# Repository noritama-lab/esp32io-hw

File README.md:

# ESP32-S3 IO Device – Hardware Repository

このリポジトリは、ESP32-S3 を産業用途で扱うための  
**入出力回路（KiCad）** と **筐体データ（FreeCAD / 3MF / STEP）** を公開するものです。

本プロジェクトは、電子工作レベルではなく、  
**工場の 24V 機器と安全に接続できる小型 I/O デバイス**  
として利用できることを目標に設計しています。

> ⚠️ 本リポジトリは個人開発によるものであり、認証・第三者検証を受けたものではありません。  
> 実運用前には、必ずご自身の環境・負荷条件に対する検証を行ってください。詳しくは [免責事項](#️-免責事項--disclaimer) を参照してください。

このハードウェアは、以下のソフトウェア群と組み合わせて使用することを想定しています。  
This hardware is designed to work together with the following software components.

- 🔧 HTTP版ファームウェア: [esp32io-firmware](https://github.com/noritama-lab/esp32io-firmware) — WiFi/HTTP経由での制御版
- 🐍 HTTP版 Pythonクライアント: [esp32io](https://pypi.org/project/esp32io/) — PyPI公開
- 🔧 MQTT版ファームウェア: [esp32io-mqtt-firmware](https://github.com/noritama-lab/esp32io-mqtt-firmware) — MQTT + Home Assistant対応ファームウェア
- 🐍 MQTT版 Pythonクライアント: [esp32io-mqtt](https://pypi.org/project/esp32io-mqtt/) — PyPI公開

---

# ESP32-S3 IO Device – Hardware Repository (English)

This repository provides the **hardware design (KiCad)** and **mechanical data (FreeCAD / 3MF / STEP)**  
for an ESP32-S3 based I/O device intended for **industrial 24V environments**.

The goal of this project is to create a compact I/O module that can be safely connected  
to factory equipment, rather than a hobby-level electronics board.

> ⚠️ This is an individually developed, open-source project. It has not been certified or independently verified.  
> Please validate the design against your own environment and load conditions before deploying it in production. See [Disclaimer](#️-disclaimer) below.

This hardware is designed to be used together with:

- 🔧 HTTP firmware: [esp32io-firmware](https://github.com/noritama-lab/esp32io-firmware) — WiFi/HTTP control variant
- 🐍 HTTP Python client: [esp32io](https://pypi.org/project/esp32io/) — Published on PyPI
- 🔧 MQTT firmware: [esp32io-mqtt-firmware](https://github.com/noritama-lab/esp32io-mqtt-firmware) — MQTT-based firmware with Home Assistant support
- 🐍 MQTT Python client: [esp32io-mqtt](https://pypi.org/project/esp32io-mqtt/) — Published on PyPI

---

## 含まれるデータ / Included Data

### ■ KiCad（回路図・基板） / KiCad (Schematics & PCB)
- `ESP32-S3-IO-DEVICE.kicad_sch` – 回路図 / Schematic  
- `ESP32-S3-IO-DEVICE.kicad_pcb` – 基板データ / PCB layout  
- `ESP32-S3-IO-DEVICE.kicad_pro` – プロジェクト設定 / Project settings  
- `sym-lib-table` / `fp-lib-table` – ライブラリ設定 / Library tables  

KiCad プロジェクトを開くだけで、  
**回路図 → 基板 → ガーバー** まで完全に再現できます。  
Opening the KiCad project allows full reproduction from **schematic → PCB → Gerber**.

基板自体はHTTP版・MQTT版どちらのファームウェアでも共通してお使いいただけます。  
The same PCB can be used with either the HTTP or MQTT firmware.

---

### ■ FreeCAD / 3D データ（筐体・取付板）  
### FreeCAD / 3D Data (Enclosure & Mounting Parts)
- `.FCStd` – FreeCAD モデル / FreeCAD models  
- `.3mf` – 3D プリント用 / For 3D printing  
- `.step` – 汎用 CAD 形式 / Standard CAD format  

ケース、基板カバー、取付板など、  
**デバイスとして使える形にするための筐体データ**を含みます。  
Includes mechanical parts required to assemble the device.

> ℹ️ 基板取付板は現行基板でもそのままご利用いただけます。  
> 基板カバーのみ旧基板に合わせた設計のため、現行基板とは適合しない場合があります。  
> 最新基板に対応した基板カバーは今後更新予定です。
>
> ℹ️ The board mounting plate is compatible with the current PCB as-is.  
> Only the board cover was designed for an older board revision and may not fit the current PCB.  
> An updated cover matching the latest board will be published in the future.

---

## 🏭 工場で使うための設計方針  
## Industrial Design Principles

本デバイスは、一般的な電子工作向けではなく、  
**工場・設備で使われる 24V 系信号を安全に扱うための回路構成**を採用しています。  
This device is designed for **industrial 24V signals**, not hobby electronics.

### ✔ DIO_OUT：NPN シンク出力 / NPN Sink Output  
PLC と同じ方式で外部ソース負荷を駆動可能。  
Compatible with PLC-style sourcing loads.

### ✔ DIO_IN：ソース入力（NPN シンク出力センサ対応）  
### Source Input (for NPN sensors)  
**トランジスタ＋抵抗＋Zener** による保護回路を採用。  
Protected using **transistor + resistors + Zener**.

### ✔ ADC：0〜10V アナログ入力 / 0–10V Analog Input  
工場のアナログ信号に合わせて **分圧＋可変抵抗＋Zener** を使用。  
Uses **voltage divider + trim resistor + Zener** for safe conversion.

> ℹ️ DI/DOはフォトカプラによりMCU側と絶縁されていますが、ADC（アナログ入力）は非絶縁です。  
> ℹ️ DI/DO channels are isolated from the MCU via optocouplers. The ADC (analog input) is **not** isolated.

### ✔ PWM：3.3V ロジック出力 / 3.3V Logic PWM  
外部ドライバ・SSR の制御信号として使用。  
Used as a control signal for external drivers or SSRs.

---

## ⚙️ 想定負荷 / Intended Load

DIO_OUT（NPNシンク出力）は、以下のような **小型DC24Vリレー** の直接駆動を想定して設計・検証しています。  
The DIO_OUT (NPN sink output) is designed and verified for driving **small DC24V relays**, such as:

- オムロン LYシリーズ相当（コイル電流 目安 20〜40mA程度） / Omron LY-series relays or equivalent (coil current approx. 20–40mA)

より大きな消費電流のソレノイド・コンタクタ・AC駆動機器を直接駆動することは想定していません。  
それらを制御する場合は、SSRやパワーリレーなど適切な中間段を介してください。  
Larger solenoids, contactors, or AC-driven devices are **not** intended to be driven directly.  
Use an appropriate intermediate stage (e.g. SSR or power relay) for such loads.

複数チャンネルを同時にON にする場合、COM+ライン全体に流れる電流（チャンネル数 × コイル電流）が、  
使用する電源・配線の許容電流を超えないことをご確認ください。  
When switching multiple channels simultaneously, verify that the total current on the COM+ line  
(number of channels × coil current) does not exceed the current rating of your power supply and wiring.

---

## ディレクトリ構成 / Directory Structure
/KiCad
/3D_print

> 📷 組み立て後の完成写真、および使用部品表（BOM）は準備中です。追って追加予定です。  
> 📷 Assembly photos and a bill of materials (BOM) are planned and will be added soon.

---

## 必要なソフトウェア / Required Software

- KiCad 7+  
- FreeCAD 0.21+  
- 3D プリンタ（任意） / Any 3D printer (FDM recommended)

---

## ⚠️ 免責事項 / Disclaimer

本リポジトリで公開する回路・筐体データは、個人による設計・検証であり、  
特定の安全規格・産業規格への適合を保証するものではありません。  
実際の設備・機器へ接続する場合は、電圧・電流・絶縁・保護協調などについて、  
利用者ご自身の責任において十分な検証を行ってください。  
本データの利用によって生じたいかなる損害についても、作者は責任を負いません。

The circuit and enclosure data provided in this repository are individually designed and verified,  
and do not guarantee compliance with any specific safety or industrial standard.  
Before connecting this device to actual equipment, users are solely responsible for verifying  
voltage, current, isolation, and protection coordination appropriate to their environment.  
The author assumes no liability for any damage resulting from the use of this data.

---

## ライセンス / License

- 回路図・基板データ（KiCad）: MIT License  
- 3D モデル（FreeCAD / STEP / 3MF）: CC BY-SA 4.0  

- Schematic & PCB (KiCad): MIT License  
- 3D Models (FreeCAD / STEP / 3MF): CC BY-SA 4.0

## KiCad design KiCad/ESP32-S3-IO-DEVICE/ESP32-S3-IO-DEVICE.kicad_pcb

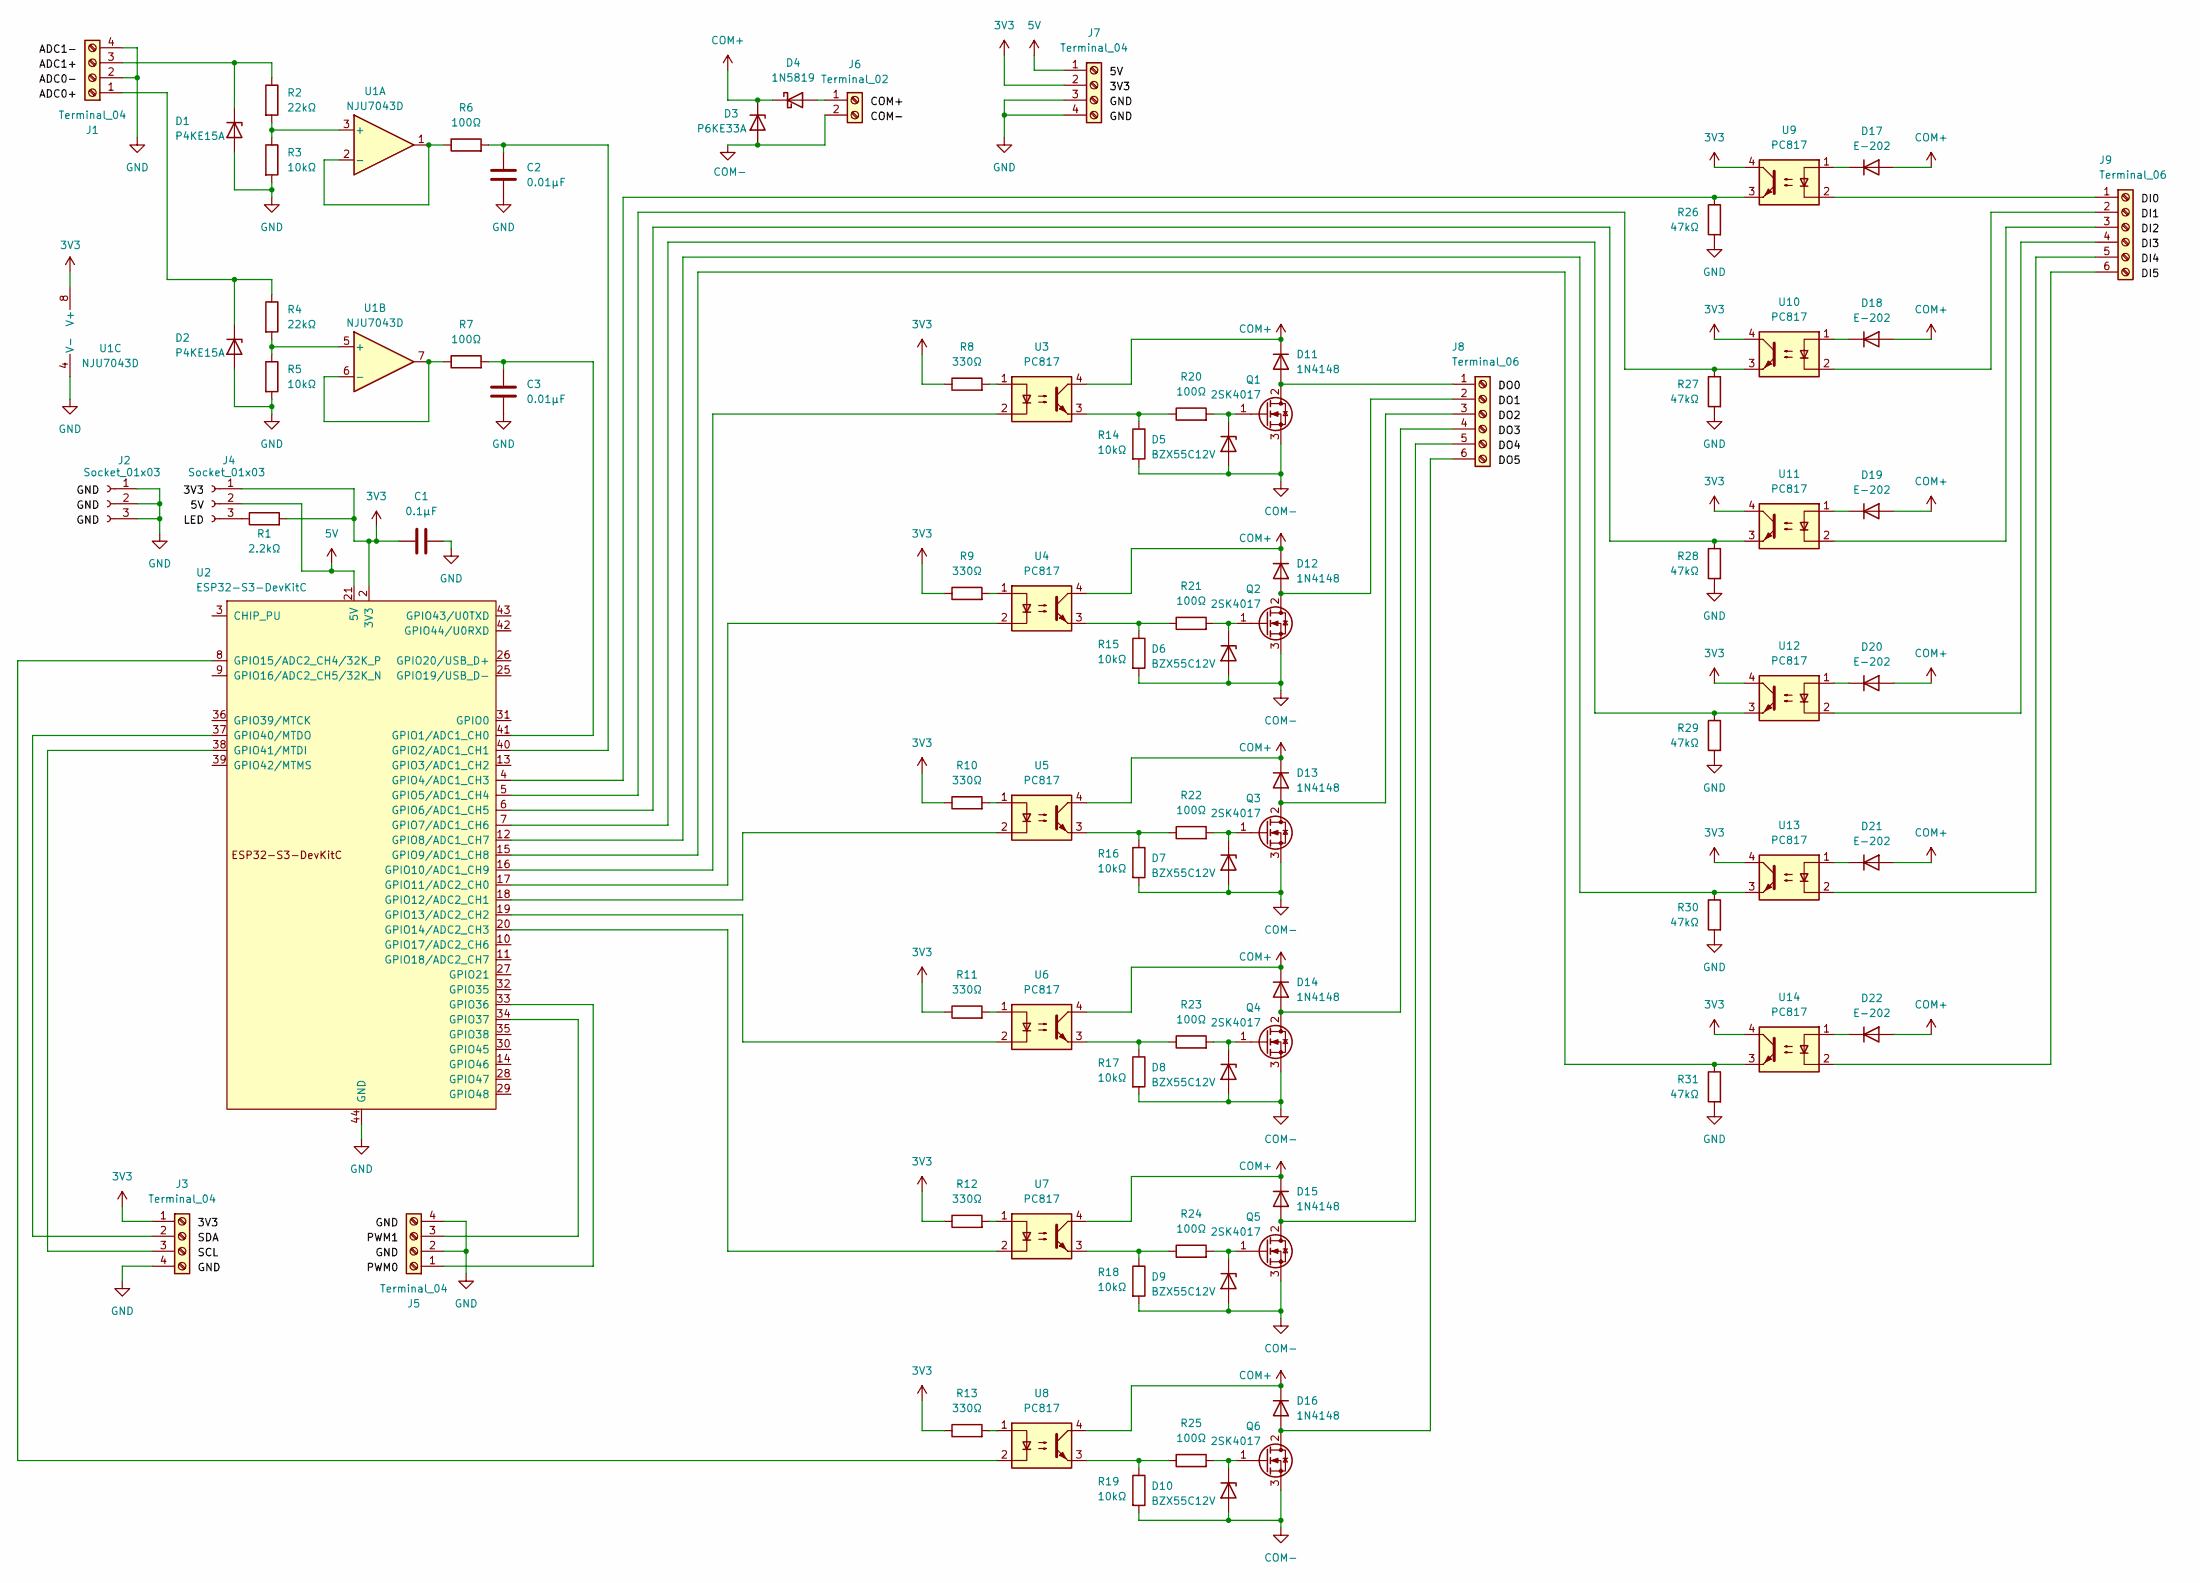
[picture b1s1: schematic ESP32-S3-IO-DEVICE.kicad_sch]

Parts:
C1: 0.1μF; C_Disc_D3.0mm_W1.6mm_P2.50mm
C2, C3: 0.01μF; C_Disc_D3.0mm_W1.6mm_P2.50mm
D1, D2: P4KE15A; D_A-405_P7.62mm_Horizontal
D3: P6KE33A; D_A-405_P7.62mm_Horizontal
D4: 1N5819; D_DO-41_SOD81_P7.62mm_Horizontal
D5, D6, D7, D8, D9, D10: BZX55C12V; D_DO-35_SOD27_P7.62mm_Horizontal
D11, D12, D13, D14, D15, D16: 1N4148; D_DO-35_SOD27_P7.62mm_Horizontal
D17, D18, D19, D20, D21, D22: E-202; D_DO-35_SOD27_P7.62mm_Horizontal
J1, J3, J5, J7: Terminal_04; TerminalBlock_Phoenix_MKDS-1,5-4-5.08_1x04_P5.08mm_Horizont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
J2, J4: Socket_01x03; PinSocket_1x03_P2.54mm_Vertical
J6: Terminal_02; TerminalBlock_Phoenix_MKDS-1,5-2-5.08_1x02_P5.08mm_Horizont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
J8, J9: Terminal_06; TerminalBlock_Phoenix_MKDS-1,5-6-5.08_1x06_P5.08mm_Horizont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
Q1, Q2, Q3, Q4, Q5, Q6: 2SK4017; TO-126-3_Vertical
R1: 2.2kΩ; R_Axial_DIN0207_L6.3mm_D2.5mm_P7.62mm_Horizontal
R2, R4: 22kΩ; R_Axial_DIN0207_L6.3mm_D2.5mm_P7.62mm_Horizontal
R3, R5, R14, R15, R16, R17, R18, R19: 10kΩ; R_Axial_DIN0207_L6.3mm_D2.5mm_P7.62mm_Horizontal
R6, R7, R20, R21, R22, R23, R24, R25: 100Ω; R_Axial_DIN0207_L6.3mm_D2.5mm_P7.62mm_Horizontal
R8, R9, R10, R11, R12, R13: 330Ω; R_Axial_DIN0207_L6.3mm_D2.5mm_P7.62mm_Horizontal
R26, R27, R28, R29, R30, R31: 47kΩ; R_Axial_DIN0207_L6.3mm_D2.5mm_P7.62mm_Horizontal
U1: NJU7043D; DIP-8_W7.62mm
U2: ESP32-S3-DevKitC; ESP32-S3-DevKitC_3rd_party
U3, U4, U5, U6, U7, U8, U9, U10, U11, U12, U13, U14: PC817; DIP-4_W7.62mm

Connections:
3V3: C1.1, J3.1, J4.1, J7.2, R1.2, R8.1, R9.1, R10.1, R11.1, R12.1, R13.1, U1.8 (V+), U2.1 (3V3), U2.2 (3V3), U9.4, U10.4, U11.4, U12.4, U13.4, U14.4
5V: J4.2, J7.1, U2.21 (5V)
COM+: D3.1 (K), D4.1 (K), D11.1 (K), D12.1 (K), D13.1 (K), D14.1 (K), D15.1 (K), D16.1 (K), D17.2 (A), D18.2 (A), D19.2 (A), D20.2 (A), D21.2 (A), D22.2 (A), U3.4, U4.4, U5.4, U6.4, U7.4, U8.4
COM-: D3.2 (A), D5.2 (A), D6.2 (A), D7.2 (A), D8.2 (A), D9.2 (A), D10.2 (A), J6.2, Q1.3 (S), Q2.3 (S), Q3.3 (S), Q4.3 (S), Q5.3 (S), Q6.3 (S), R14.2, R15.2, R16.2, R17.2, R18.2, R19.2
GND: C1.2, C2.2, C3.2, D1.2 (A), D2.2 (A), J1.2, J1.4, J2.1, J2.2, J2.3, J3.4, J5.2, J5.4, J7.3, J7.4, R3.2, R5.2, R26.2, R27.2, R28.2, R29.2, R30.2, R31.2, U1.4 (V-), U2.22 (GND), U2.23 (GND), U2.24 (GND), U2.44 (GND)
unnamed: D1.1 (K), J1.3, R2.1
unnamed: D2.1 (K), J1.1, R4.1
unnamed: D4.2 (A), J6.1
unnamed: D5.1 (K), Q1.1 (G), R20.2
unnamed: D6.1 (K), Q2.1 (G), R21.2
unnamed: D7.1 (K), Q3.1 (G), R22.2
unnamed: D8.1 (K), Q4.1 (G), R23.2
unnamed: D9.1 (K), Q5.1 (G), R24.2
unnamed: D10.1 (K), Q6.1 (G), R25.2
unnamed: D11.2 (A), J8.1, Q1.2 (D)
unnamed: D12.2 (A), J8.2, Q2.2 (D)
unnamed: D13.2 (A), J8.3, Q3.2 (D)
unnamed: D14.2 (A), J8.4, Q4.2 (D)
unnamed: D15.2 (A), J8.5, Q5.2 (D)
unnamed: D16.2 (A), J8.6, Q6.2 (D)
unnamed: D17.1 (K), U9.1
unnamed: D18.1 (K), U10.1
unnamed: D19.1 (K), U11.1
unnamed: D20.1 (K), U12.1
unnamed: D21.1 (K), U13.1
unnamed: D22.1 (K), U14.1
unnamed: J3.2, U2.37 (GPIO40/MTDO)
unnamed: J3.3, U2.38 (GPIO41/MTDI)
unnamed: J4.3, R1.1
unnamed: J5.1, U2.33 (GPIO36)
unnamed: J5.3, U2.34 (GPIO37)
unnamed: J9.1, U9.2
unnamed: J9.2, U10.2
unnamed: J9.3, U11.2
unnamed: J9.4, U12.2
unnamed: J9.5, U13.2
unnamed: J9.6, U14.2
unnamed: R8.2, U3.1
unnamed: R9.2, U4.1
unnamed: R10.2, U5.1
unnamed: R11.2, U6.1
unnamed: R12.2, U7.1
unnamed: R13.2, U8.1
unnamed: R14.1, R20.1, U3.3
unnamed: R15.1, R21.1, U4.3
unnamed: R16.1, R22.1, U5.3
unnamed: R17.1, R23.1, U6.3
unnamed: R18.1, R24.1, U7.3
unnamed: R19.1, R25.1, U8.3
unnamed: R2.2, R3.1, U1.3 (+)
unnamed: R6.1, U1.1, U1.2 (-)
unnamed: R4.2, R5.1, U1.5 (+)
unnamed: R7.1, U1.6 (-), U1.7
unnamed: C3.1, R7.2, U2.41 (GPIO1/ADC1_CH0)
unnamed: C2.1, R6.2, U2.40 (GPIO2/ADC1_CH1)
unnamed: R26.1, U2.4 (GPIO4/ADC1_CH3), U9.3
unnamed: R27.1, U2.5 (GPIO5/ADC1_CH4), U10.3
unnamed: R28.1, U2.6 (GPIO6/ADC1_CH5), U11.3
unnamed: R29.1, U2.7 (GPIO7/ADC1_CH6), U12.3
unnamed: R30.1, U2.12 (GPIO8/ADC1_CH7), U13.3
unnamed: R31.1, U2.15 (GPIO9/ADC1_CH8), U14.3
unnamed: U2.16 (GPIO10/ADC1_CH9), U3.2
unnamed: U2.17 (GPIO11/ADC2_CH0), U4.2
unnamed: U2.18 (GPIO12/ADC2_CH1), U5.2
unnamed: U2.19 (GPIO13/ADC2_CH2), U6.2
unnamed: U2.20 (GPIO14/ADC2_CH3), U7.2
unnamed: U2.8 (GPIO15/ADC2_CH4/32K_P), U8.2

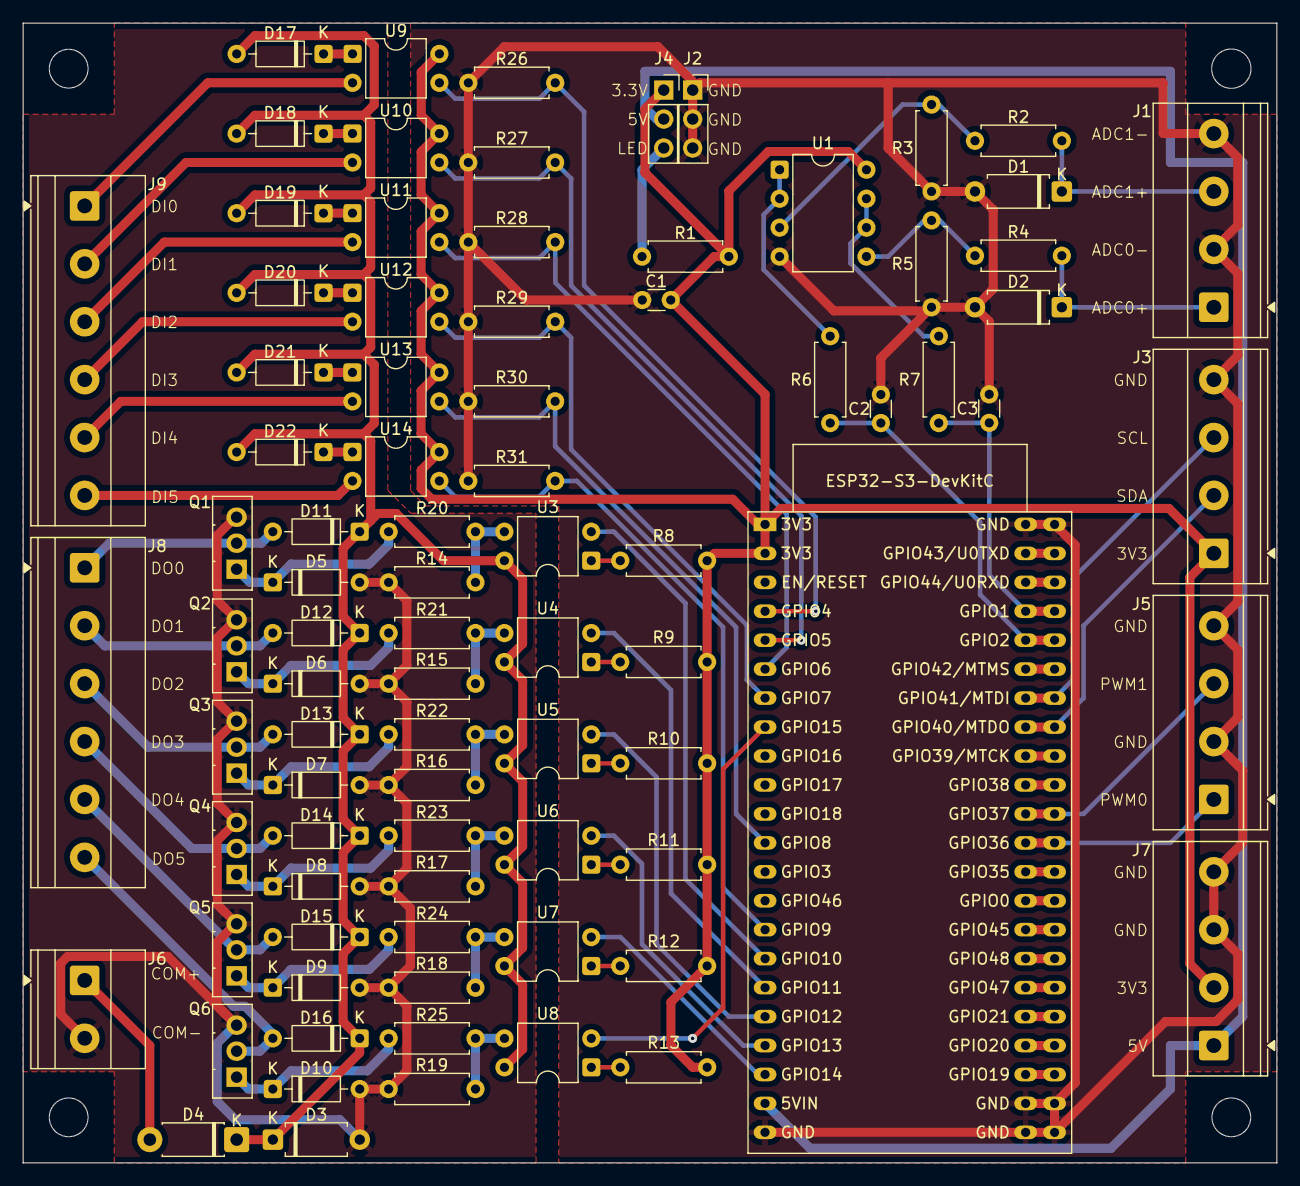
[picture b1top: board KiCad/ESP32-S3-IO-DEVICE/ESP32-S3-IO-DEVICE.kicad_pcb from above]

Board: 2 copper layers, 110.0 x 100.0 mm, 85 parts (0 on the bottom side), 67 nets.

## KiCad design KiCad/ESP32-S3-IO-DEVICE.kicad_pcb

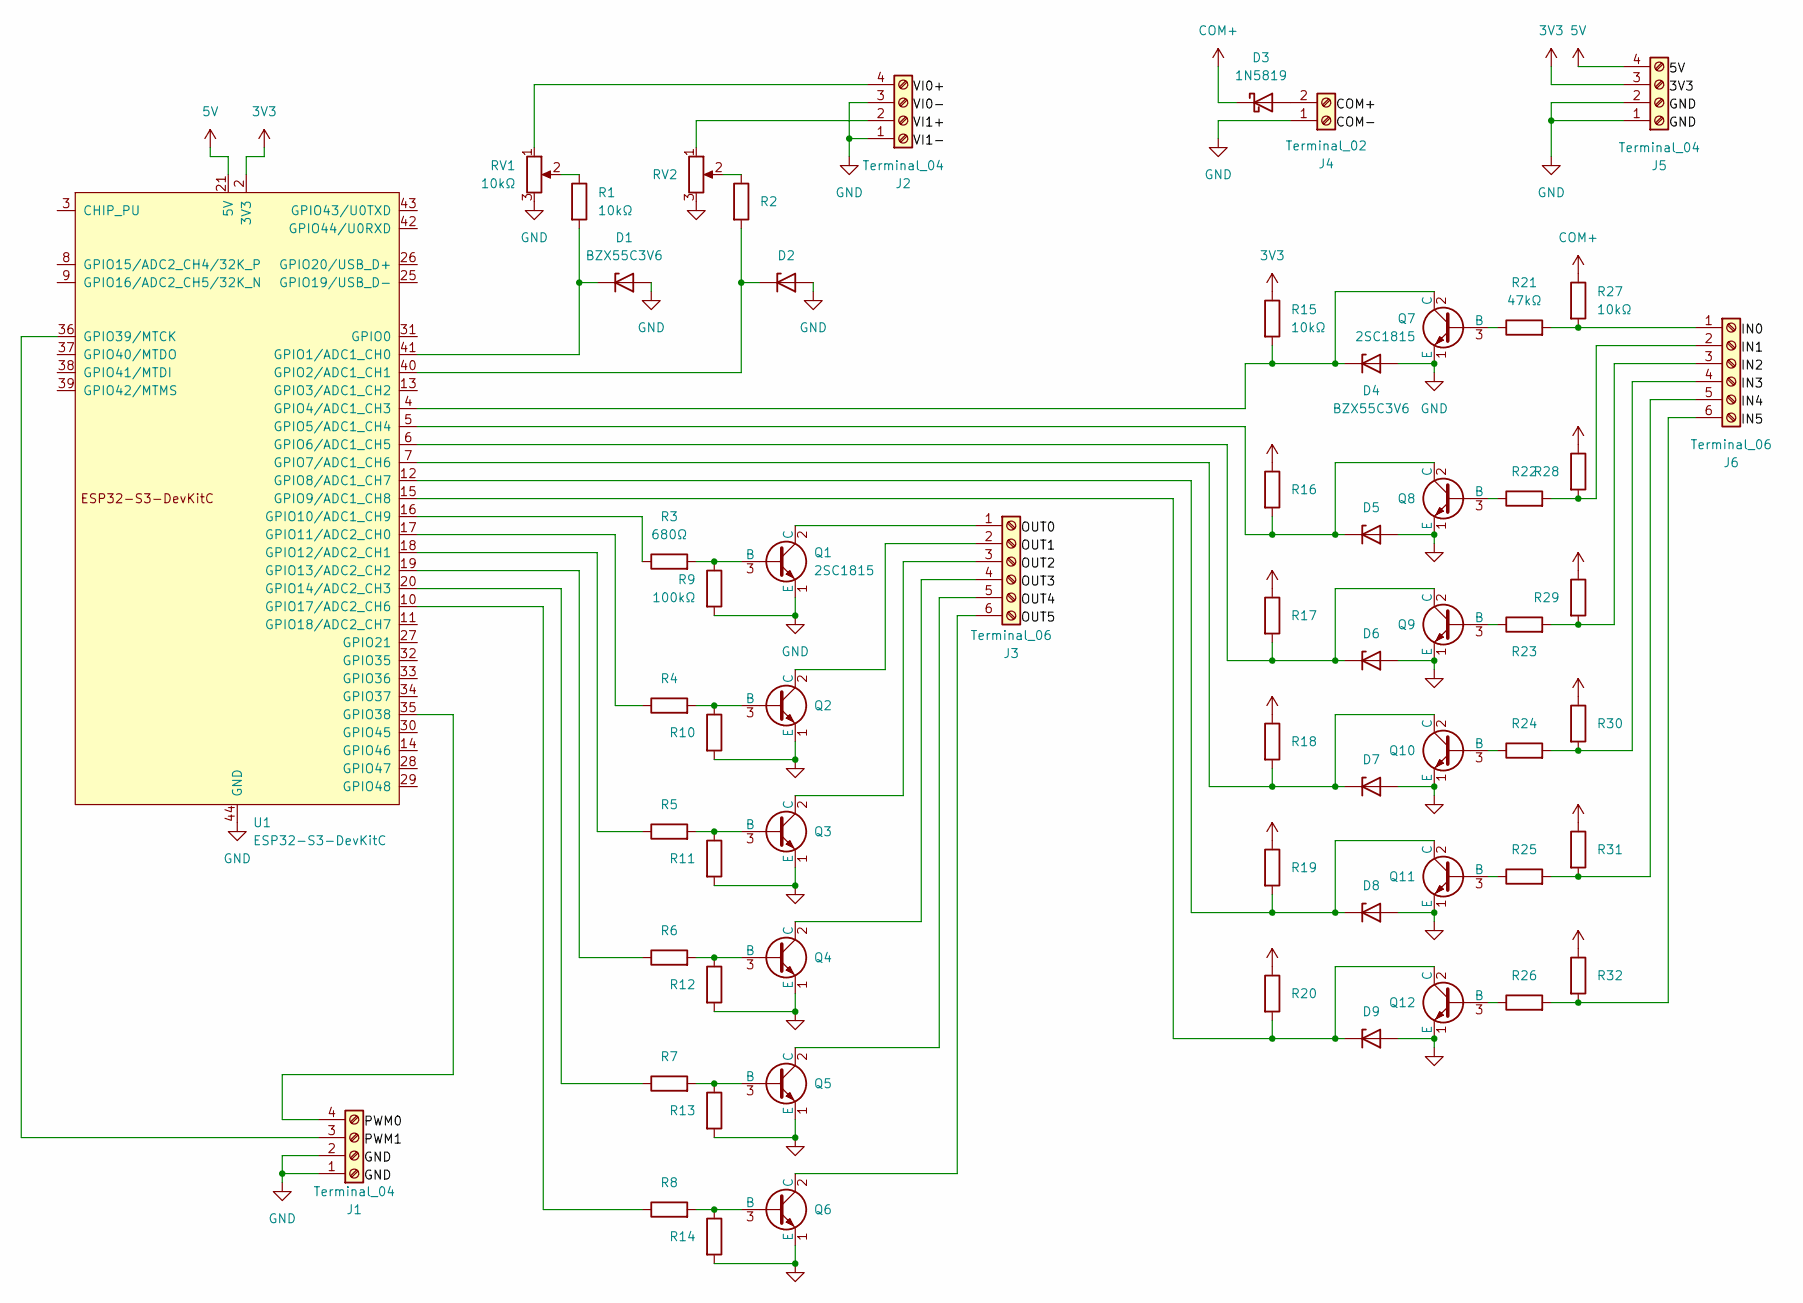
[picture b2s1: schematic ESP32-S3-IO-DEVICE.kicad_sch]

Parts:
D1, D2, D4, D5, D6, D7, D8, D9: BZX55C3V6; D_DO-35_SOD27_P7.62mm_Horizontal
D3: 1N5819; D_DO-41_SOD81_P10.16mm_Horizontal
J1, J2, J5: Terminal_04; TerminalBlock_Phoenix_MKDS-1,5-4-5.08_1x04_P5.08mm_Horizont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
J3, J6: Terminal_06; TerminalBlock_Phoenix_MKDS-1,5-6-5.08_1x06_P5.08mm_Horizont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
J4: Terminal_02; TerminalBlock_Phoenix_MKDS-1,5-2-5.08_1x02_P5.08mm_Horizont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
Q1, Q2, Q3, Q4, Q5, Q6, Q7, Q8, Q9, Q10, Q11, Q12: 2SC1815; TO-92_Inline
R1, R2, R15, R16, R17, R18, R19, R20, R27, R28, R29, R30, R31, R32: 10kΩ; R_Axial_DIN0207_L6.3mm_D2.5mm_P7.62mm_Horizontal
R3, R4, R5, R6, R7, R8: 680Ω; R_Axial_DIN0207_L6.3mm_D2.5mm_P7.62mm_Horizontal
R9, R10, R11, R12, R13, R14: 100kΩ; R_Axial_DIN0207_L6.3mm_D2.5mm_P7.62mm_Horizontal
R21, R22, R23, R24, R25, R26: 47kΩ; R_Axial_DIN0207_L6.3mm_D2.5mm_P7.62mm_Horizontal
RV1, RV2: 10kΩ; Potentiometer_Bourns_3386P_Vertical
U1: ESP32-S3-DevKitC; ESP32-S3-DevKitC-1

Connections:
3V3: J5.3, R15.1, R16.1, R17.1, R18.1, R19.1, R20.1, U1.1 (3V3), U1.2 (3V3)
5V: J5.4, U1.21 (5V)
COM+: D3.1 (K), R27.1, R28.1, R29.1, R30.1, R31.1, R32.1
GND: D1.2 (A), D2.2 (A), D4.2 (A), D5.2 (A), D6.2 (A), D7.2 (A), D8.2 (A), D9.2 (A), J1.1, J1.2, J2.1, J2.3, J4.1, J5.1, J5.2, Q1.1 (E), Q2.1 (E), Q3.1 (E), Q4.1 (E), Q5.1 (E), Q6.1 (E), Q7.1 (E), Q8.1 (E), Q9.1 (E), Q10.1 (E), Q11.1 (E), Q12.1 (E), R9.2, R10.2, R11.2, R12.2, R13.2, R14.2, RV1.3, RV2.3, U1.22 (GND), U1.23 (GND), U1.24 (GND), U1.44 (GND)
unnamed: D1.1 (K), R1.2, U1.41 (GPIO1/ADC1_CH0)
unnamed: D2.1 (K), R2.2, U1.40 (GPIO2/ADC1_CH1)
unnamed: D3.2 (A), J4.2
unnamed: D4.1 (K), Q7.2 (C), R15.2, U1.4 (GPIO4/ADC1_CH3)
unnamed: D5.1 (K), Q8.2 (C), R16.2, U1.5 (GPIO5/ADC1_CH4)
unnamed: D6.1 (K), Q9.2 (C), R17.2, U1.6 (GPIO6/ADC1_CH5)
unnamed: D7.1 (K), Q10.2 (C), R18.2, U1.7 (GPIO7/ADC1_CH6)
unnamed: D8.1 (K), Q11.2 (C), R19.2, U1.12 (GPIO8/ADC1_CH7)
unnamed: D9.1 (K), Q12.2 (C), R20.2, U1.15 (GPIO9/ADC1_CH8)
unnamed: J1.3, U1.36 (GPIO39/MTCK)
unnamed: J1.4, U1.35 (GPIO38)
unnamed: J2.2, RV2.1
unnamed: J2.4, RV1.1
unnamed: J3.1, Q1.2 (C)
unnamed: J3.2, Q2.2 (C)
unnamed: J3.3, Q3.2 (C)
unnamed: J3.4, Q4.2 (C)
unnamed: J3.5, Q5.2 (C)
unnamed: J3.6, Q6.2 (C)
unnamed: J6.1, R21.2, R27.2
unnamed: J6.2, R22.2, R28.2
unnamed: J6.3, R23.2, R29.2
unnamed: J6.4, R24.2, R30.2
unnamed: J6.5, R25.2, R31.2
unnamed: J6.6, R26.2, R32.2
unnamed: Q1.3 (B), R3.2, R9.1
unnamed: Q2.3 (B), R4.2, R10.1
unnamed: Q3.3 (B), R5.2, R11.1
unnamed: Q4.3 (B), R6.2, R12.1
unnamed: Q5.3 (B), R7.2, R13.1
unnamed: Q6.3 (B), R8.2, R14.1
unnamed: Q7.3 (B), R21.1
unnamed: Q8.3 (B), R22.1
unnamed: Q9.3 (B), R23.1
unnamed: Q10.3 (B), R24.1
unnamed: Q11.3 (B), R25.1
unnamed: Q12.3 (B), R26.1
unnamed: R1.1, RV1.2
unnamed: R2.1, RV2.2
unnamed: R3.1, U1.16 (GPIO10/ADC1_CH9)
unnamed: R4.1, U1.17 (GPIO11/ADC2_CH0)
unnamed: R5.1, U1.18 (GPIO12/ADC2_CH1)
unnamed: R6.1, U1.19 (GPIO13/ADC2_CH2)
unnamed: R7.1, U1.20 (GPIO14/ADC2_CH3)
unnamed: R8.1, U1.10 (GPIO17/ADC2_CH6)

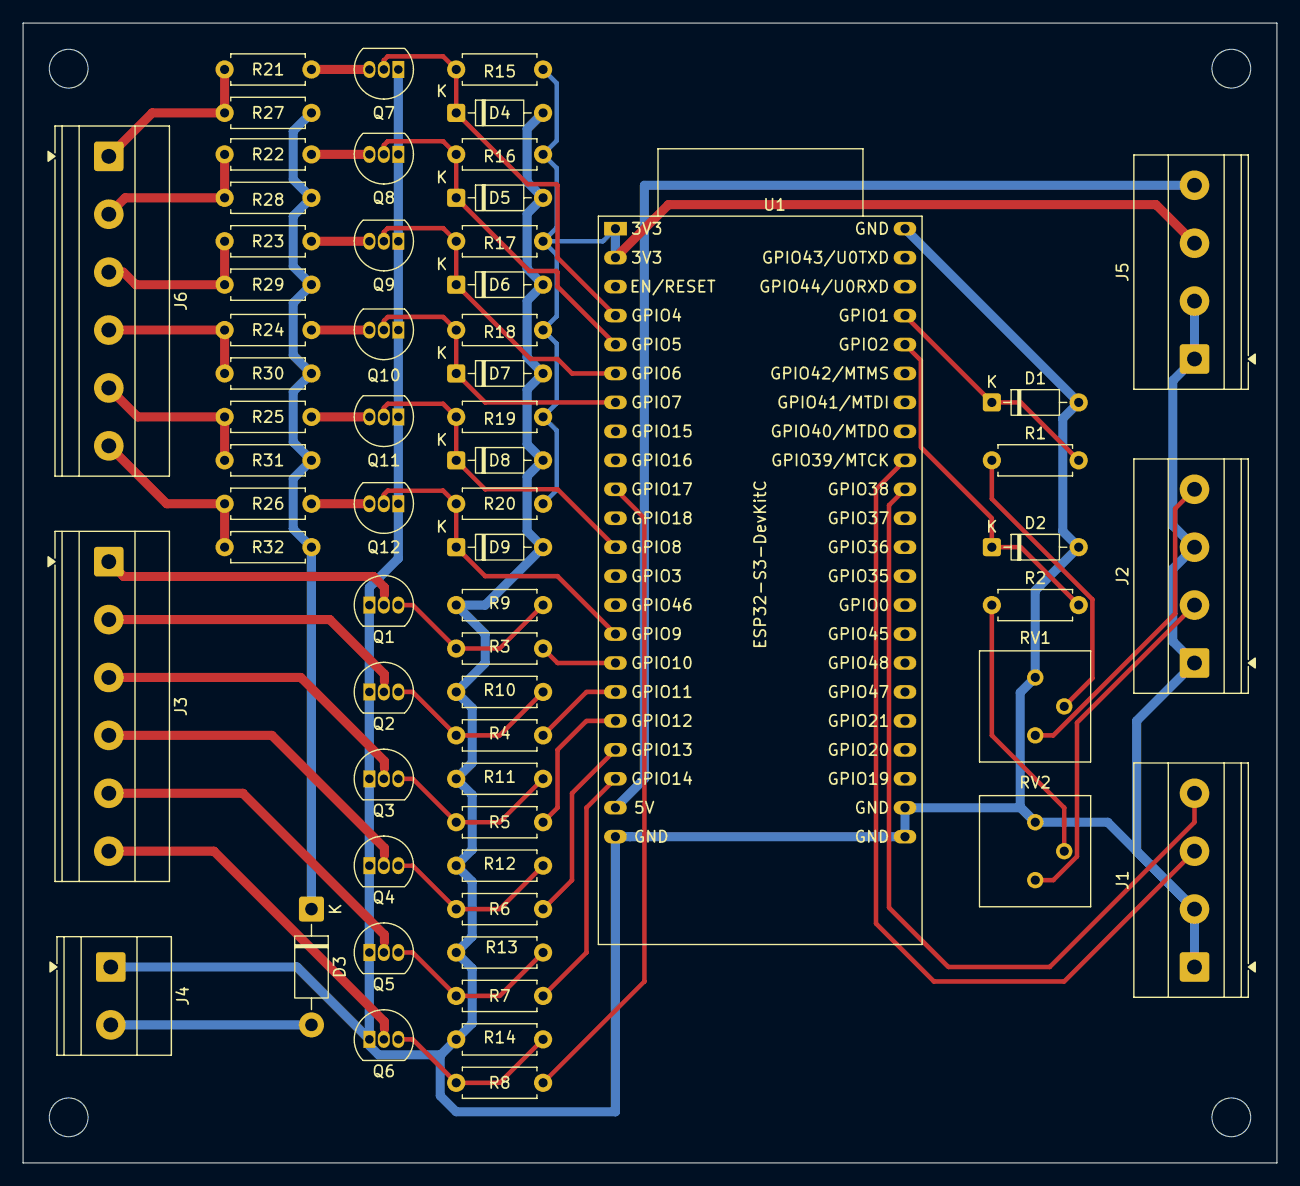
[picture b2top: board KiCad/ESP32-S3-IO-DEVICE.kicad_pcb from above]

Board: 2 copper layers, 110.0 x 100.0 mm, 62 parts (0 on the bottom side), 49 nets.

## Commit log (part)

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2026-03-24 Add 3D data
2026-03-24 Add README to KiCad folder
2026-03-24 fixed
2026-04-03 Edit ESP32-S3-PythonGUI.fzz
2026-04-06 Update schematic: fix wiring errors and improve component labeling
2026-04-07 Normalize line endings (LF) for KiCad and project files
2026-04-14 Update .gitignore and remove ignored files
2026-04-14 Normalize line endings
2026-06-20 Prepare ESP32IO for public release
